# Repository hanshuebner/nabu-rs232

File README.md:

# NABU PC RS232 card

This card is designed to be compatible with the original NABU RS232
controller, but to not require an extra option adapter.

Work in progress, not ready for production!

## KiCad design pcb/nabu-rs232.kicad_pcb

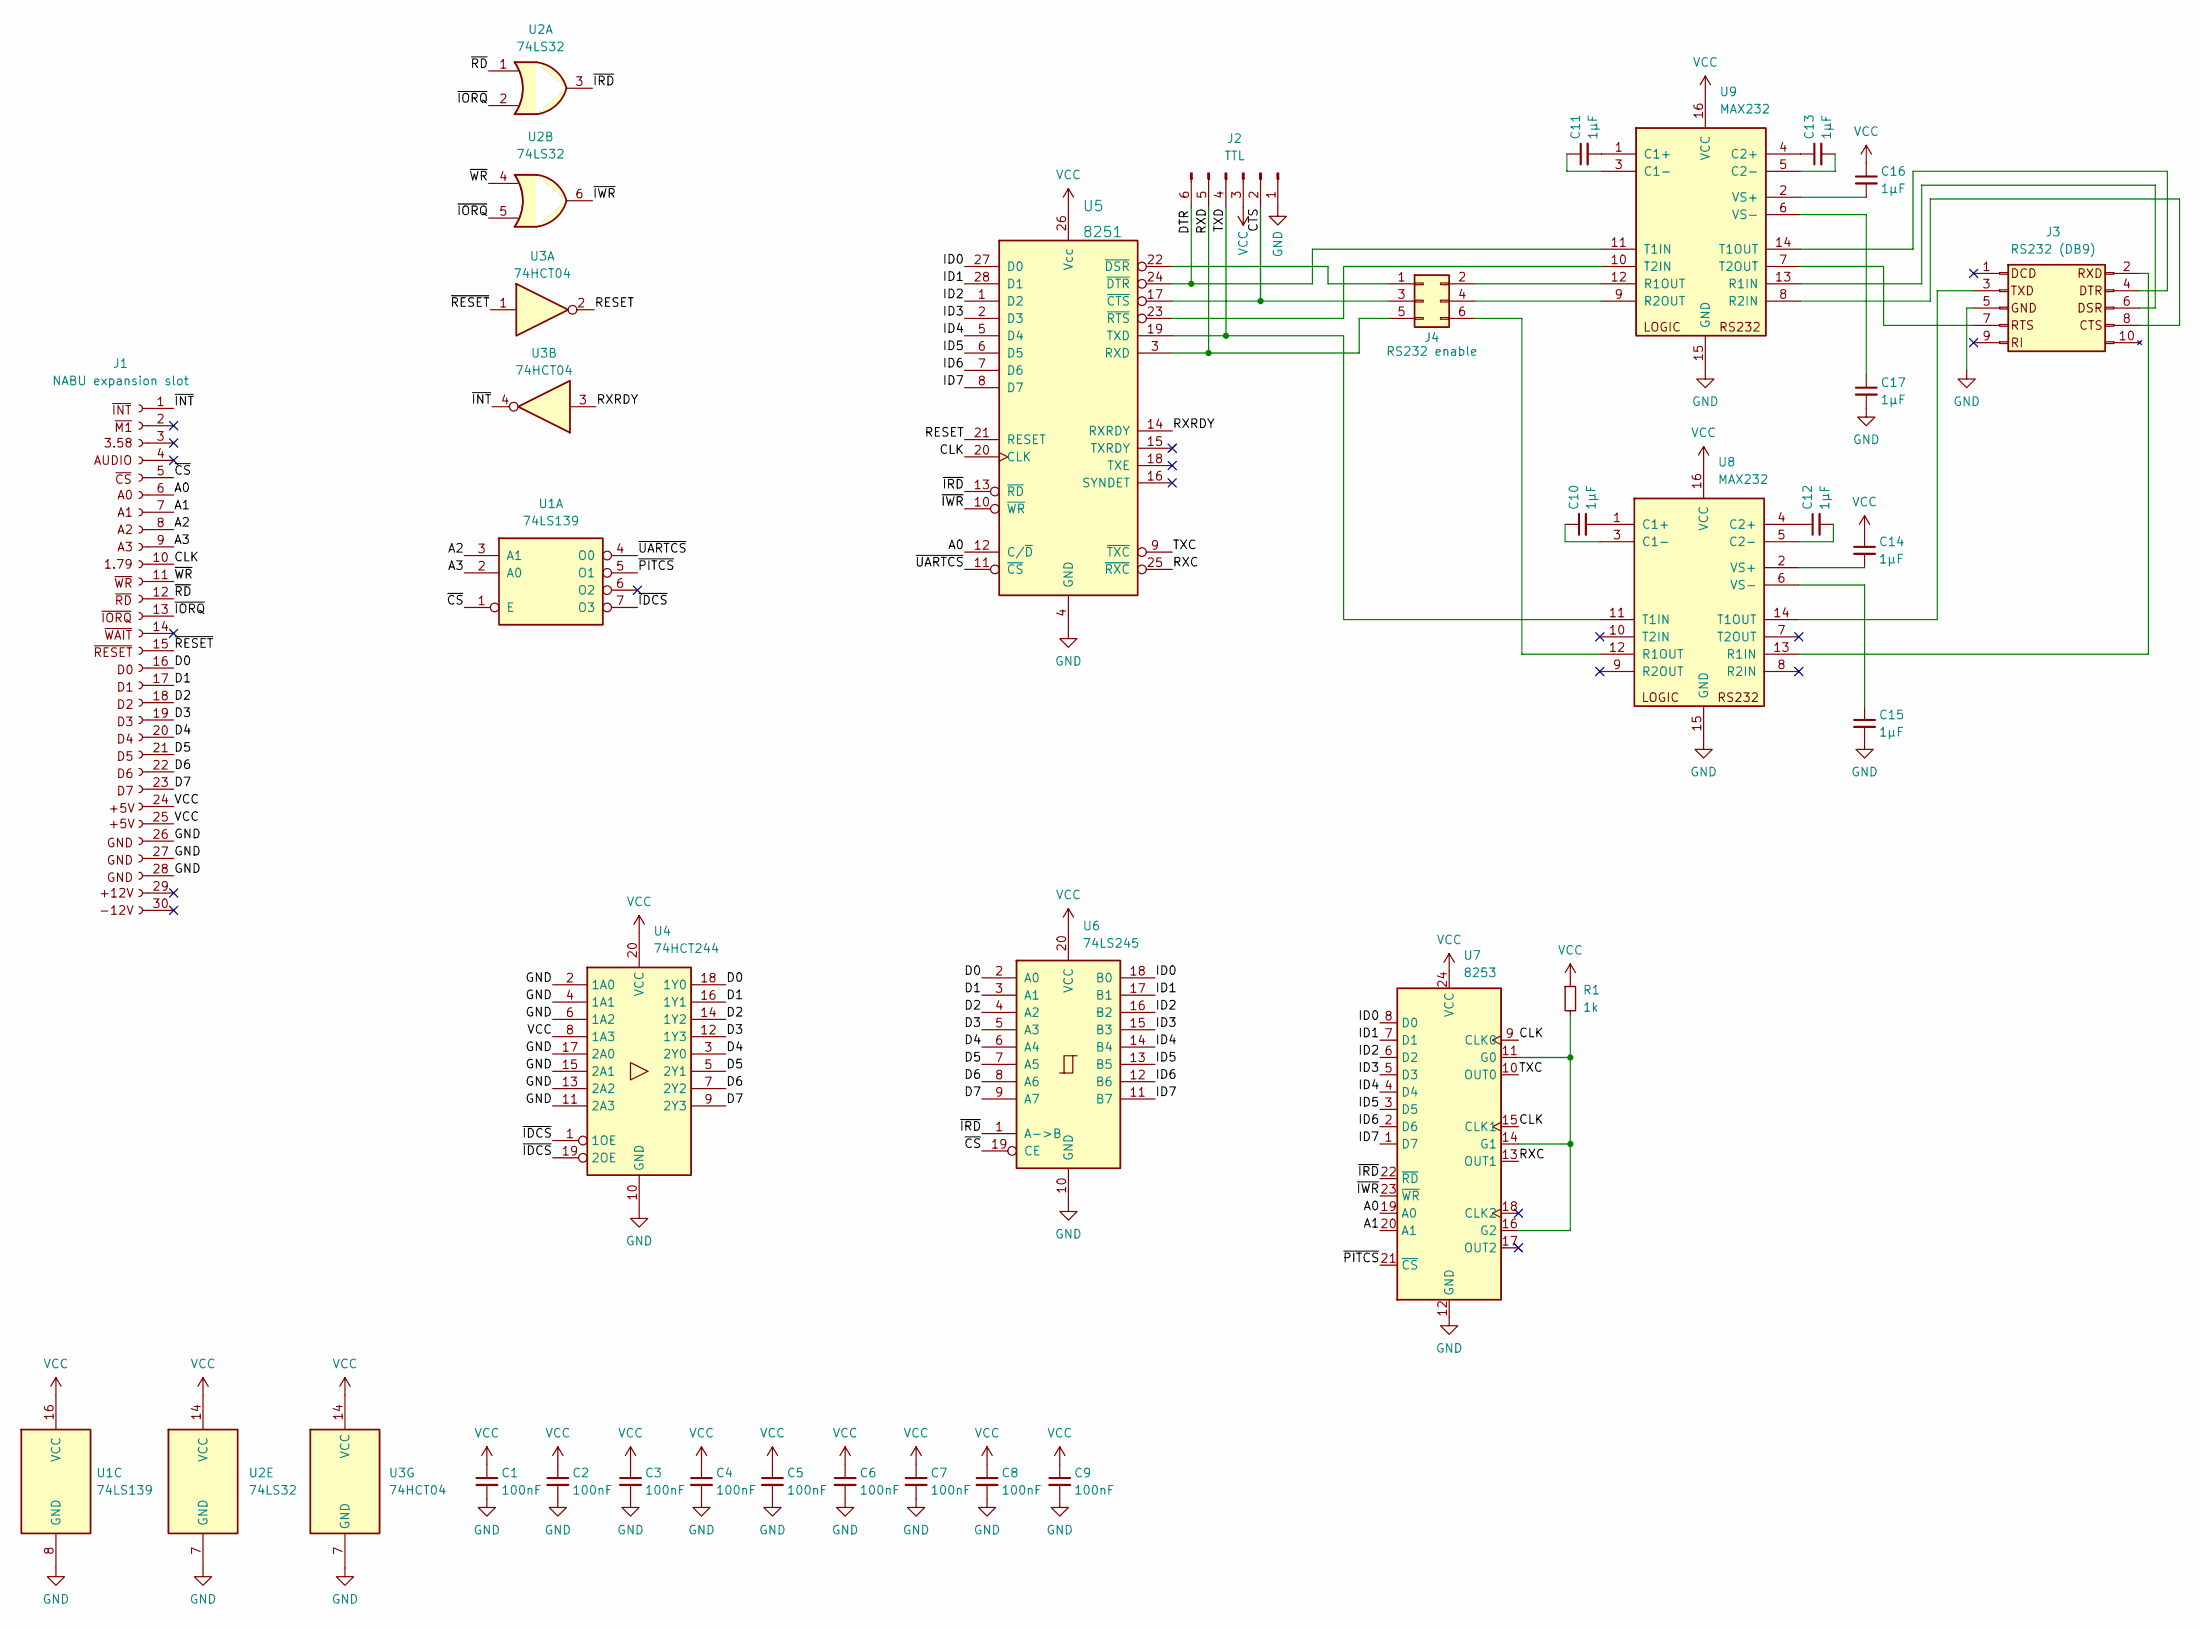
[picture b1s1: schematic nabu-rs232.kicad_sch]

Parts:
C1, C2, C3, C4, C5, C6, C7, C8, C9: 100nF; C_0603_1608Metric_Pad1.08x0.95mm_HandSolder
C10, C11, C12, C13, C14, C15, C16, C17: 1µF; C_0603_1608Metric_Pad1.08x0.95mm_HandSolder
J1: NABU expansion slot; NABU_Option_Connector
J2: TTL; PinHeader_1x06_P2.54mm_Horizontal
J3: RS232 (DB9); PinHeader_2x05_P2.54mm_Horizontal
J4: RS232 enable; PinHeader_2x03_P2.54mm_Vertical
R1: 1k; R_0805_2012Metric_Pad1.20x1.40mm_HandSolder
U1: 74LS139; SOP-16_4.55x10.3mm_P1.27mm
U2: 74LS32; SOP-14_4.55x10.3mm_P1.27mm
U3: 74HCT04; SOP-14_4.55x10.3mm_P1.27mm
U4: 74HCT244; SOP-20_7.5x12.8mm_P1.27mm
U5: 8251; DIP-28_W15.24mm
U6: 74LS245; SOP-20_7.5x12.8mm_P1.27mm
U7: 8253; DIP-24_W15.24mm
U8, U9: MAX232; SOP-16_4.55x10.3mm_P1.27mm

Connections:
/A0: J1.6 (A0), U5.12 (C/~D), U7.19 (A0)
/A1: J1.7 (A1), U7.20 (A1)
/A2: J1.8 (A2), U1.3 (A1)
/A3: J1.9 (A3), U1.2 (A0)
/CLK: J1.10 (1.79), U5.20 (CLK), U7.9 (CLK0), U7.15 (CLK1)
/CTS: J2.2, J4.3, U5.17 (~CTS)
/D0: J1.16 (D0), U4.18 (1Y0), U6.2 (A0)
/D1: J1.17 (D1), U4.16 (1Y1), U6.3 (A1)
/D2: J1.18 (D2), U4.14 (1Y2), U6.4 (A2)
/D3: J1.19 (D3), U4.12 (1Y3), U6.5 (A3)
/D4: J1.20 (D4), U4.3 (2Y0), U6.6 (A4)
/D5: J1.21 (D5), U4.5 (2Y1), U6.7 (A5)
/D6: J1.22 (D6), U4.7 (2Y2), U6.8 (A6)
/D7: J1.23 (D7), U4.9 (2Y3), U6.9 (A7)
/DTR: J2.6, U5.24 (~DTR), U9.11 (T1IN)
/ID0: U5.27 (D0), U6.18 (B0), U7.8 (D0)
/ID1: U5.28 (D1), U6.17 (B1), U7.7 (D1)
/ID2: U5.1 (D2), U6.16 (B2), U7.6 (D2)
/ID3: U5.2 (D3), U6.15 (B3), U7.5 (D3)
/ID4: U5.5 (D4), U6.14 (B4), U7.4 (D4)
/ID5: U5.6 (D5), U6.13 (B5), U7.3 (D5)
/ID6: U5.7 (D6), U6.12 (B6), U7.2 (D6)
/ID7: U5.8 (D7), U6.11 (B7), U7.1 (D7)
/RESET: U3.2, U5.21 (RESET)
/RXC: U5.25 (~RXC), U7.13 (OUT1)
/RXD: J2.5, J4.5, U5.3 (RXD)
/RXRDY: U3.3, U5.14 (RXRDY)
/TXC: U5.9 (~TXC), U7.10 (OUT0)
/TXD: J2.4, U5.19 (TXD), U8.11 (T1IN)
/~CS: J1.5 (~CS), U1.1 (E), U6.19 (CE)
/~IDCS: U1.7 (O3), U4.1 (1OE), U4.19 (2OE)
/~INT: J1.1 (~INT), U3.4
/~IORQ: J1.13 (~IORQ), U2.2, U2.5
/~IRD: U2.3, U5.13 (~RD), U6.1 (A->B), U7.22 (~RD)
/~IWR: U2.6, U5.10 (~WR), U7.23 (~WR)
/~PITCS: U1.5 (O1), U7.21 (~CS)
/~RD: J1.12 (~RD), U2.1
/~RESET: J1.15 (~RESET), U3.1
/~UARTCS: U1.4 (O0), U5.11 (~CS)
/~WR: J1.11 (~WR), U2.4
GND: C1.2, C2.2, C3.2, C4.2, C5.2, C6.2, C7.2, C8.2, C9.2, C15.2, C17.2, J1.26 (GND), J1.27 (GND), J1.28 (GND), J2.1, J3.5, U1.8 (GND), U2.7 (GND), U3.7 (GND), U4.2 (1A0), U4.4 (1A1), U4.6 (1A2), U4.10 (GND), U4.11 (2A3), U4.13 (2A2), U4.15 (2A1), U4.17 (2A0), U5.4 (GND), U6.10 (GND), U7.12 (GND), U8.15 (GND), U9.15 (GND)
unnamed: C10.1, U8.3 (C1-)
unnamed: C10.2, U8.1 (C1+)
unnamed: C11.1, U9.3 (C1-)
unnamed: C11.2, U9.1 (C1+)
unnamed: C12.1, U8.4 (C2+)
unnamed: C12.2, U8.5 (C2-)
unnamed: C13.1, U9.4 (C2+)
unnamed: C13.2, U9.5 (C2-)
unnamed: C14.2, U8.2 (VS+)
unnamed: C15.1, U8.6 (VS-)
unnamed: C16.2, U9.2 (VS+)
unnamed: C17.1, U9.6 (VS-)
unnamed: J4.1, U5.22 (~DSR)
unnamed: J4.2, U9.12 (R1OUT)
unnamed: J4.4, U9.9 (R2OUT)
unnamed: J4.6, U8.12 (R1OUT)
unnamed: R1.2, U7.11 (G0), U7.14 (G1), U7.16 (G2)
unnamed: U5.23 (~RTS), U9.10 (T2IN)
unnamed: J3.2 (RXD), U8.13 (R1IN)
unnamed: J3.3 (TXD), U8.14 (T1OUT)
unnamed: J3.7 (RTS), U9.7 (T2OUT)
unnamed: J3.8 (CTS), U9.8 (R2IN)
unnamed: J3.6 (DSR), U9.13 (R1IN)
unnamed: J3.4 (DTR), U9.14 (T1OUT)
VCC: C1.1, C2.1, C3.1, C4.1, C5.1, C6.1, C7.1, C8.1, C9.1, C14.1, C16.1, J1.24 (+5V), J1.25 (+5V), J2.3, R1.1, U1.16 (VCC), U2.14 (VCC), U3.14 (VCC), U4.8 (1A3), U4.20 (VCC), U5.26 (Vcc), U6.20 (VCC), U7.24 (VCC), U8.16 (VCC), U9.16 (VCC)

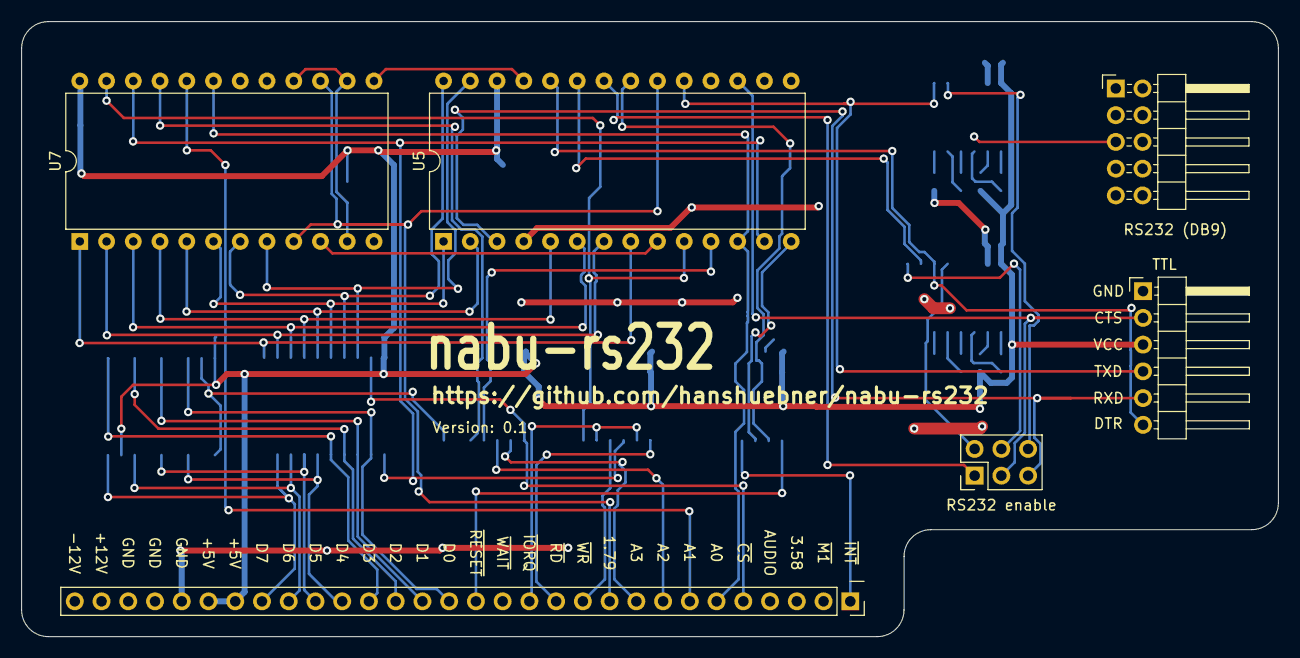
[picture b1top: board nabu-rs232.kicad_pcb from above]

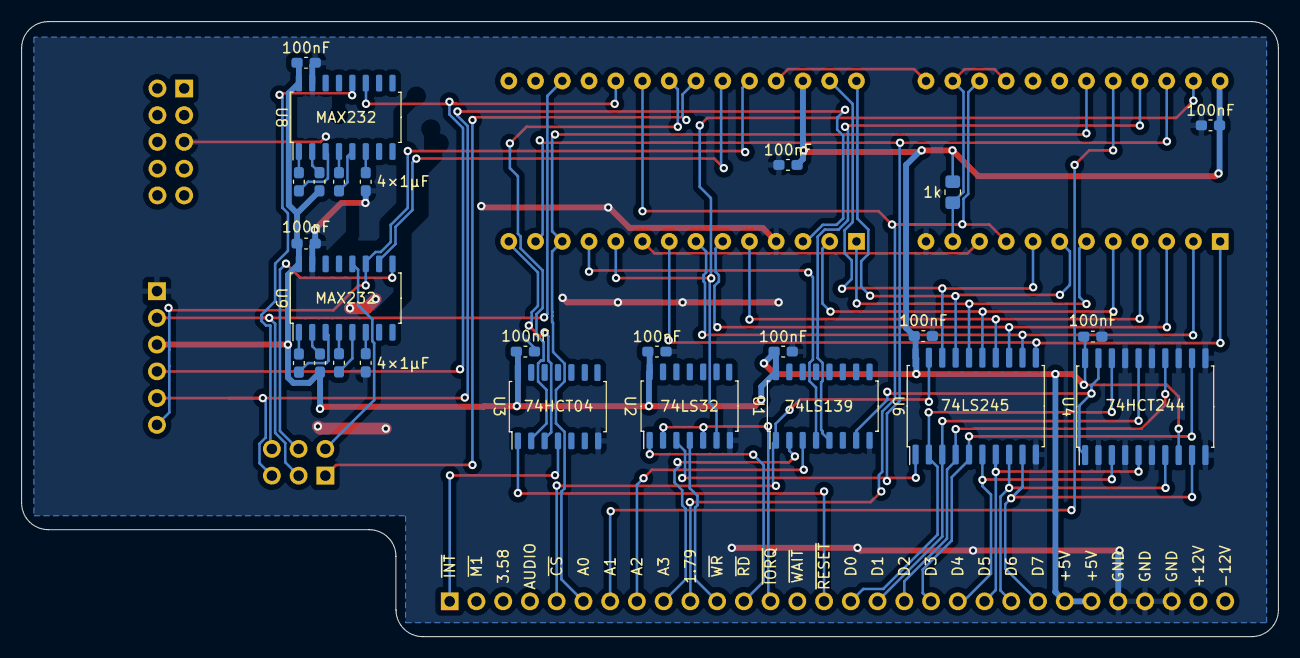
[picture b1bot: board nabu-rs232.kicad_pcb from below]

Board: 2 copper layers, 119.4 x 58.4 mm, 31 parts (25 on the bottom side), 66 nets.

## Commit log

2023-02-05 Add README.md
2023-02-05 rearrange
2023-02-05 Fix filename
2023-02-16 version 0.1 sent to jlcpcb
2023-02-24 Use proper DB9 RS232 pinout
